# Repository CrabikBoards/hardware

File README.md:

# crabik

Репозиторий с файлами дизайна платы для KiCad 5.1

|                 Вид сверху                |                Вид снизу                |
|-------------------------------------------|-----------------------------------------|
|  |  |

## Описание

crabik это недорогая плата для изучения языка программирования [Rust](https://www.rust-lang.org/). Мозгом платы является микроконтроллер nRF52810. Плата имеет встроенный отладчик, основанный на CMSIS-DAP.

## Производство

Инструкция для заказа производства платы и монтажа на сервисе JLCPCB содержится в файле [PRODUCTION](PRODUCTION.md).

## Лицензия

Оборудование выпущено под лицензией CERN Open Hardware License v1.2. См. Файл [LICENSE](LICENSE) для получения дополнительной информации.

## Поддержка
Поддержите Амперку и оборудование с открытым исходным кодом, покупая продукты на [Amperka.ru](https://amperka.ru/)!

## Социальные сети Амперки

https://www.youtube.com/user/AmperkaRu

https://vk.com/amperkaru

https://www.instagram.com/amperkaru

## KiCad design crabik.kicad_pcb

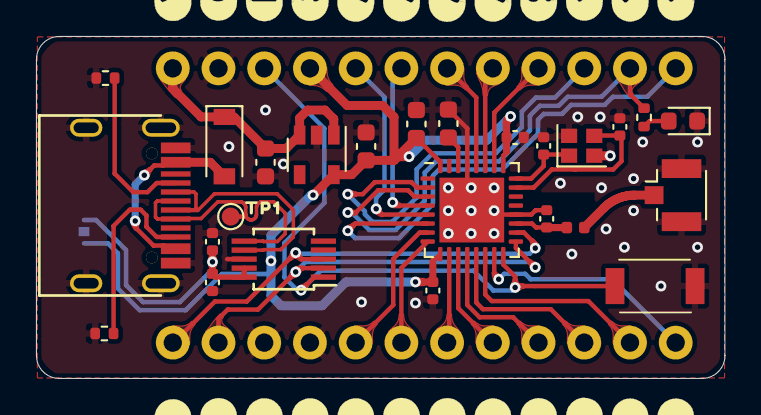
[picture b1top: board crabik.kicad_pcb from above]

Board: 2 copper layers, 38.3 x 19.0 mm, 29 parts (1 on the bottom side), 34 nets.

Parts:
ANT1: U.FL-R-SMT-1; U.FL_Hirose_U.FL-R-SMT-1_Vertical
C1: 0.8pF; C_0402_1005Metric
C2, C3: 12pF; C_0402_1005Metric
C4, C5, C8, C9: 100nF; C_0402_1005Metric
C6: 4.7uF; C_0603_1608Metric
C7, C10, C11: 1uF; C_0603_1608Metric
D1: MBR0520; D_SOD-123
D2: LED; LED_0603_1608Metric
J1: Left; 1X12_NO_SILK
J2: Right; 1X12_NO_SILK
JP2: CMSIS-DAP Programmer ON; SolderJumper-2_P1.3mm_Bridged_Pad1.0x1.5mm
L1: 3.9nH; L_0402_1005Metric
OSHW_Mono_0.25_Scale: RU00003; OSHW_Mono_0.25_Scale
P1: USB-C; TYPE-C16PIN
R1, R2: 5.1K; R_0402_1005Metric
R3: 1.5K; R_0402_1005Metric
SW1: Reset button; TS-1088R-02526
TP2: BOOT; TestPoint_Pad_D1.0mm
U1: CH552E (or CH554E); MSOP-10_3x3mm_P0.5mm
U2: nRF52810-QCxx; QFN-32-1EP_5x5mm_P0.5mm_EP3.6x3.6mm
U3: AP2112K-3.3; SOT-23-5
Y1: 32MHz; Crystal_SMD_2016-4Pin_2.0x1.6mm

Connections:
3.3v: C4.2, C5.2, C6.2, C11.2, J2.4, JP2.1, U2.9, U2.25, U2.32, U3.5
5v: D1.2, P1.A4
A0: J2.5, U2.5
A1: J2.6, U2.4
A2: J2.7, U2.28
A3: J2.8, U2.27
D1: J1.5, U2.7
D2: J1.6, U2.8
D3: J1.7, U2.10
D4: J1.8, U2.11
D5: J1.9, U2.12
D6: J1.10, U2.13
D7: J1.11, U2.14
D8: J1.12, U2.15
D9: J2.9, U2.26
D10: J2.10, U2.2
D11: J2.11, R3.2, U2.3
D12: J2.12, U2.6
D+: P1.A6, TP2.1, U1.6
D-: P1.A7, U1.7
GND: ANT1.2, C1.1, C2.1, C3.1, C4.1, C5.1, C6.1, C7.1, C8.2, C9.2, C10.1, C11.1, D2.1, J1.3, J1.4, J2.2, P1.A1, P1.S1, R1.1, R2.1, SW1.2, U1.8, U2.20, U2.29, U2.33, U3.2, Y1.2, Y1.4
unnamed: ANT1.1, L1.1
unnamed: C1.2, L1.2, U2.19
unnamed: C2.2, U2.23, Y1.3
unnamed: C3.2, U2.24, Y1.1
unnamed: C7.2, U2.30
unnamed: C8.1, C9.1, JP2.2, U1.9, U1.10
unnamed: D2.2, R3.1
unnamed: P1.A5, R1.2
unnamed: P1.B5, R2.2
RESET: J2.3, SW1.1, U1.1, U2.16
SWDCLK: J1.2, U1.2, U2.17
SWDIO: J1.1, U1.3, U2.18
VCC: C10.2, D1.1, J2.1, U3.1, U3.3

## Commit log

2021-03-24 Первый коммит (revB)
2021-03-25 Удаление лишнего
2021-04-16 Добавление информации и файлов для производства
2021-04-16 fix gitignore
2021-04-16 fix production directory
2021-05-11 Добавление инструкций с прошивкой CH554 (в роли отладчика)
